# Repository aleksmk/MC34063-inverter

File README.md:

Simple invernter based on the famous MC34063 chip.

Vin:    5V (± 0.5V)
Vout:   -12V
Iout:   100mA

It's based from the application note in the MC34063 datasheet. The inductor used here is a 100uH one.

Cheers.

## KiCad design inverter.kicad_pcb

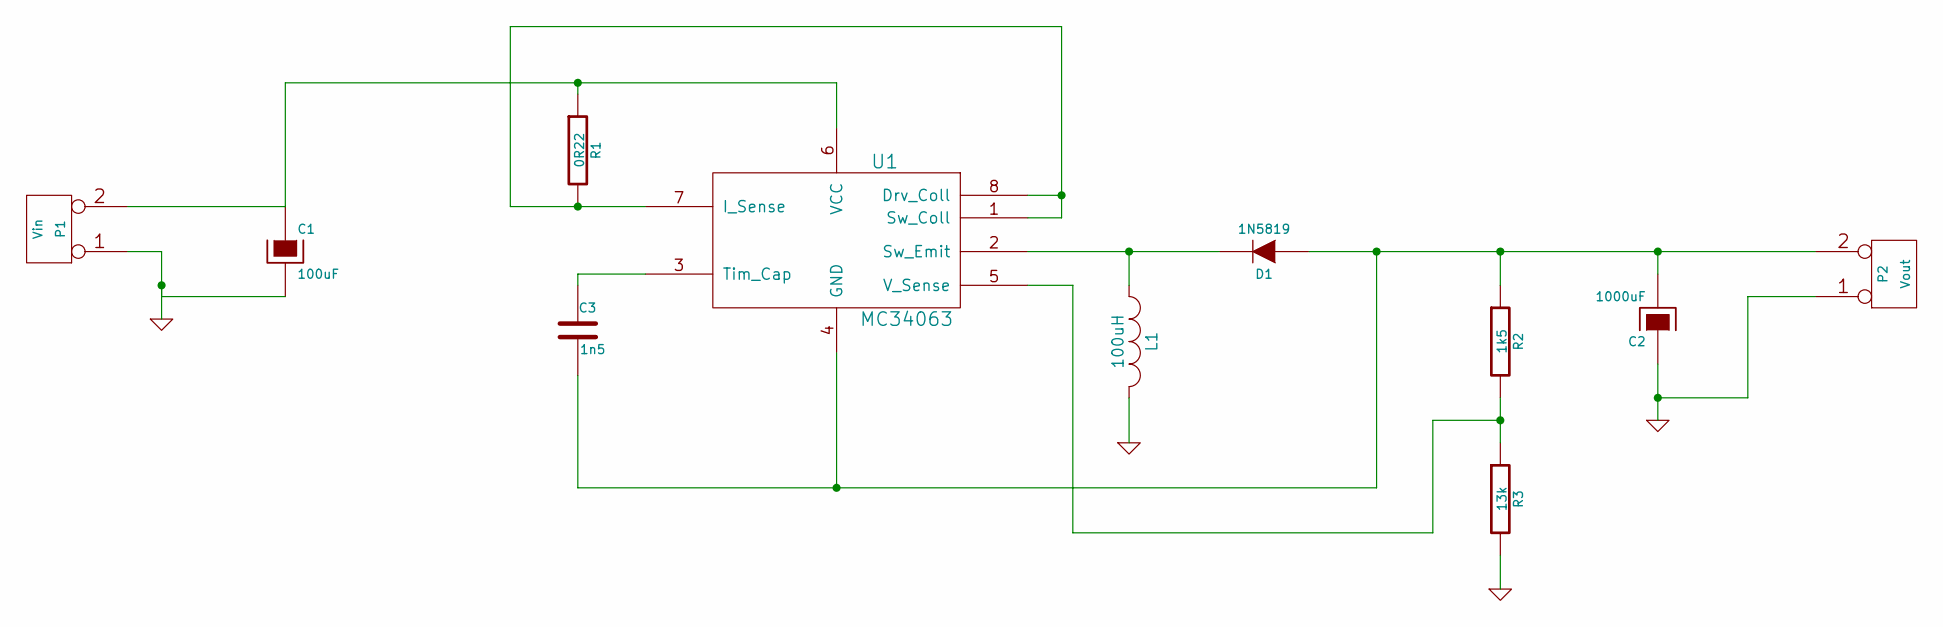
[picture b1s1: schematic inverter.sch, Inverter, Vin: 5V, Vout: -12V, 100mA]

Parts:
C1: 100uF
C2: 1000uF
C3: 1n5
D1: 1N5819
L1: 100uH
P1: Vin
P2: Vout
R1: 0R22
R2: 1k5
R3: 13k
U1: MC34063

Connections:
GND: C1.2, C2.1, L1.2, P1.1, P2.1, R3.2
unnamed: D1.2 (K), L1.1, U1.2 (Sw_Emit)
unnamed: R2.2, R3.1, U1.5 (V_Sense)
unnamed: C2.2, C3.2, D1.1 (A), P2.2 (PM), R2.1, U1.4 (GND)
unnamed: C3.1, U1.3 (Tim_Cap)
unnamed: C1.1, P1.2 (PM), R1.1, U1.6 (VCC)
unnamed: R1.2, U1.1 (Sw_Coll), U1.7 (I_Sense), U1.8 (Drv_Coll)

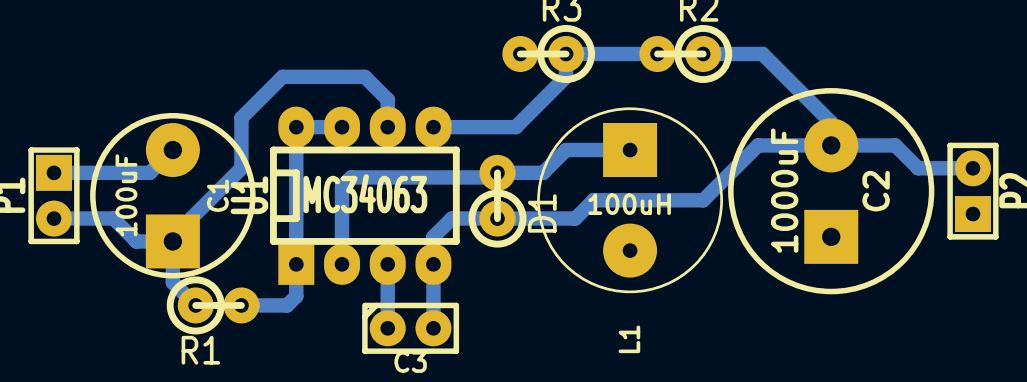
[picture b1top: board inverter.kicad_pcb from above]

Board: 2 copper layers, 11 parts (0 on the bottom side), 7 nets.

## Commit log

2014-11-05 MC34063 Inverter
2014-11-05 A short description
